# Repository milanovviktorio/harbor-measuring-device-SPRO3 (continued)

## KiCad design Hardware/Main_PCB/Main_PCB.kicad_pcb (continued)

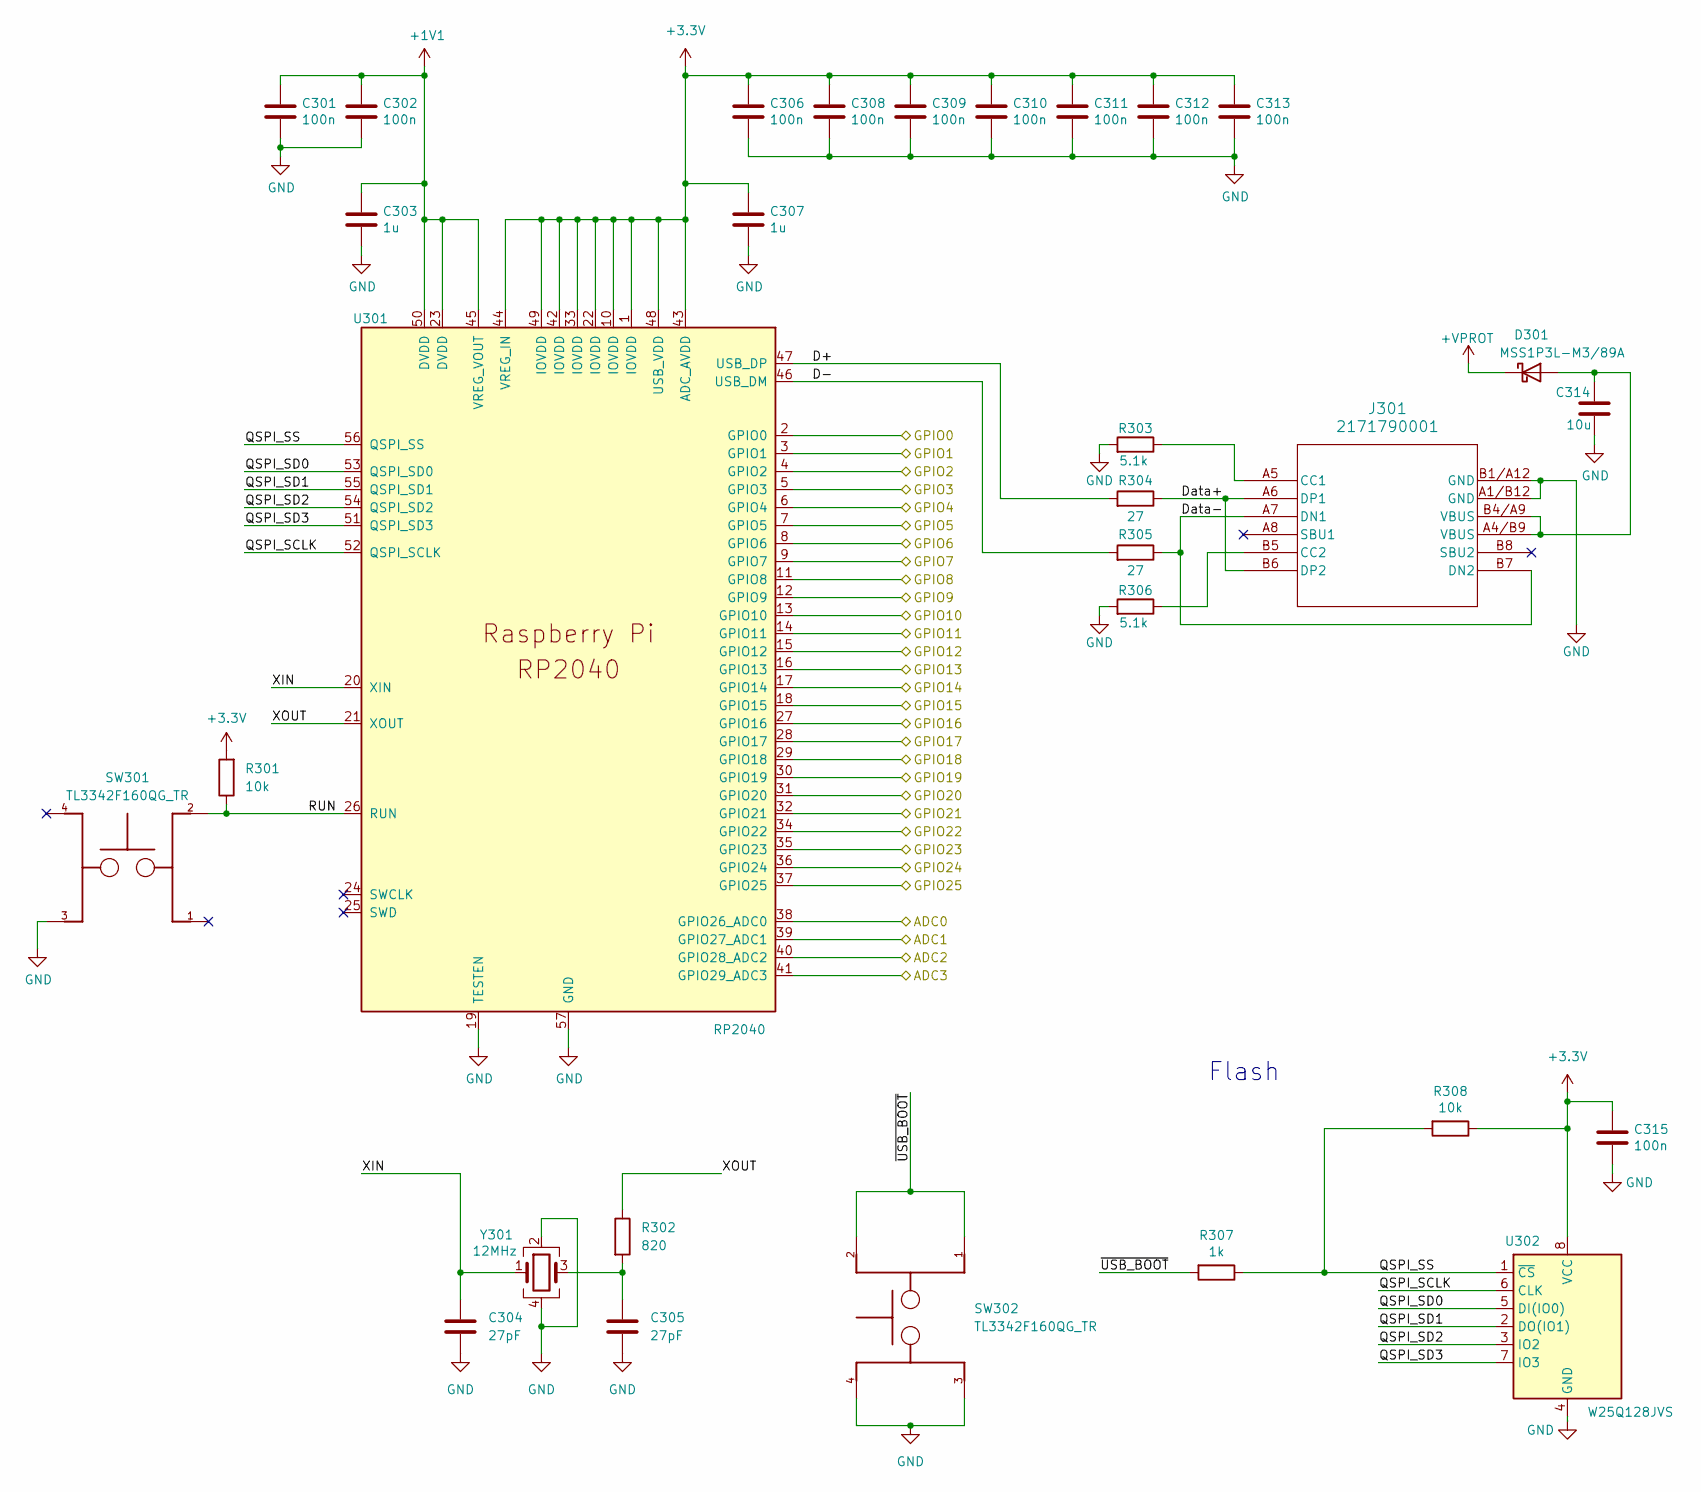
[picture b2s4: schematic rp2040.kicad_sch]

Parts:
C301, C302, C306, C308, C309, C310, C311, C312, C313, C315: 100n; C_0603_1608Metric_Pad1.08x0.95mm_HandSolder
C303, C307: 1u; C_0603_1608Metric_Pad1.08x0.95mm_HandSolder
C304, C305: 27pF; C_0603_1608Metric_Pad1.08x0.95mm_HandSolder
C314: 10u; C_0603_1608Metric_Pad1.08x0.95mm_HandSolder
D301: MSS1P3L-M3/89A; Vishay_SMPA
J301: 2171790001; 2171790001_MOL
R301: 10k; C_0603_1608Metric_Pad1.08x0.95mm_HandSolder
R302: 820; R_0603_1608Metric_Pad0.98x0.95mm_HandSolder
R303, R306: 5.1k; R_0603_1608Metric_Pad0.98x0.95mm_HandSolder
R304, R305: 27; R_0603_1608Metric_Pad0.98x0.95mm_HandSolder
R307: 1k; R_0603_1608Metric_Pad0.98x0.95mm_HandSolder
R308: 10k; R_0603_1608Metric_Pad0.98x0.95mm_HandSolder
SW301, SW302: TL3342F160QG_TR; SW_TL3342F160QG_TR
U301: RP2040; QFN-56-1EP_7x7mm_P0.4mm_EP3.2x3.2mm
U302: W25Q128JVS; SOIC-8_5.3x5.3mm_P1.27mm
Y301: 12MHz; Crystal_SMD_Abracon_ABM8G-4Pin_3.2x2.5mm

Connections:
+1V1: C301.1, C302.1, C303.1, U301.23 (DVDD), U301.45 (VREG_VOUT), U301.50 (DVDD)
+3.3V: C306.1, C307.1, C308.1, C309.1, C310.1, C311.1, C312.1, C313.1, C315.1, R301.2, R308.1, U301.1 (IOVDD), U301.10 (IOVDD), U301.22 (IOVDD), U301.33 (IOVDD), U301.42 (IOVDD), U301.43 (ADC_AVDD), U301.44 (VREG_IN), U301.48 (USB_VDD), U301.49 (IOVDD), U302.8 (VCC); also elsewhere on the board
+VPROT: D301.1 (K); also elsewhere on the board
/AHS: U301.37 (GPIO25); also elsewhere on the board
/ALS: U301.36 (GPIO24); also elsewhere on the board
/BEMF: U301.8 (GPIO6); also elsewhere on the board
/BHS: U301.35 (GPIO23); also elsewhere on the board
/BLS: U301.34 (GPIO22); also elsewhere on the board
/CE: U301.9 (GPIO7); also elsewhere on the board
/CHS: U301.32 (GPIO21); also elsewhere on the board
/CLS: U301.31 (GPIO20); also elsewhere on the board
/CSN: U301.11 (GPIO8); also elsewhere on the board
/ICM42688 - Gyro/AP_CS: U301.12 (GPIO9); also elsewhere on the board
/ICM42688 - Gyro/AP_SCL: U301.14 (GPIO11); also elsewhere on the board
/ICM42688 - Gyro/AP_SDA: U301.13 (GPIO10); also elsewhere on the board
/ICM42688 - Gyro/AP_SDO: U301.16 (GPIO13); also elsewhere on the board
/ICM42688 - Gyro/INT1: U301.15 (GPIO12); also elsewhere on the board
/MISO: U301.27 (GPIO16); also elsewhere on the board
/MOSI: U301.30 (GPIO19); also elsewhere on the board
/OUT3: U301.17 (GPIO14); also elsewhere on the board
/OUT4: U301.18 (GPIO15); also elsewhere on the board
/Power supply unit/Battery_voltage_level: U301.39 (GPIO27_ADC1); also elsewhere on the board
/RP2040/ADC0: U301.38 (GPIO26_ADC0); also elsewhere on the board
/RP2040/ADC2: U301.40 (GPIO28_ADC2)
/RP2040/ADC3: U301.41 (GPIO29_ADC3)
/RP2040/D+: R304.2, U301.47 (USB_DP)
/RP2040/D-: R305.2, U301.46 (USB_DM)
/RP2040/Data+: J301.A6 (DP1), J301.B6 (DP2), R304.1
/RP2040/Data-: J301.A7 (DN1), J301.B7 (DN2), R305.1
/RP2040/GPIO0: U301.2 (GPIO0); also elsewhere on the board
/RP2040/GPIO1: U301.3 (GPIO1); also elsewhere on the board
/RP2040/GPIO2: U301.4 (GPIO2); also elsewhere on the board
/RP2040/GPIO3: U301.5 (GPIO3); also elsewhere on the board
/RP2040/GPIO4: U301.6 (GPIO4); also elsewhere on the board
/RP2040/GPIO5: U301.7 (GPIO5); also elsewhere on the board
/RP2040/QSPI_SCLK: U301.52 (QSPI_SCLK), U302.6 (CLK)
/RP2040/QSPI_SD0: U301.53 (QSPI_SD0), U302.5 (DI(IO0))
/RP2040/QSPI_SD1: U301.55 (QSPI_SD1), U302.2 (DO(IO1))
/RP2040/QSPI_SD2: U301.54 (QSPI_SD2), U302.3 (IO2)
/RP2040/QSPI_SD3: U301.51 (QSPI_SD3), U302.7 (IO3)
/RP2040/QSPI_SS: R307.1, R308.2, U301.56 (QSPI_SS), U302.1 (~CS)
/RP2040/RUN: R301.1, SW301.2, U301.26 (RUN)
/RP2040/XIN: C304.1, U301.20 (XIN), Y301.1
/RP2040/XOUT: R302.1, U301.21 (XOUT)
/RP2040/~USB_BOOT: R307.2, SW302.1, SW302.2
/SCK: U301.29 (GPIO18); also elsewhere on the board
/Servo_In: U301.28 (GPIO17); also elsewhere on the board
GND: C301.2, C302.2, C303.2, C304.2, C305.2, C306.2, C307.2, C308.2, C309.2, C310.2, C311.2, C312.2, C313.2, C314.2, C315.2, J301.A1/B12 (GND), J301.B1/A12 (GND), R303.2, R306.2, SW301.3, SW302.3, SW302.4, U301.19 (TESTEN), U301.57 (GND), U302.4 (GND), Y301.2, Y301.4; also elsewhere on the board
unnamed: C305.1, R302.2, Y301.3
unnamed: C314.1, D301.2 (A), J301.A4/B9 (VBUS), J301.B4/A9 (VBUS)
unnamed: J301.A5 (CC1), R303.1
unnamed: J301.B5 (CC2), R306.1

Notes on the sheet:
Flash

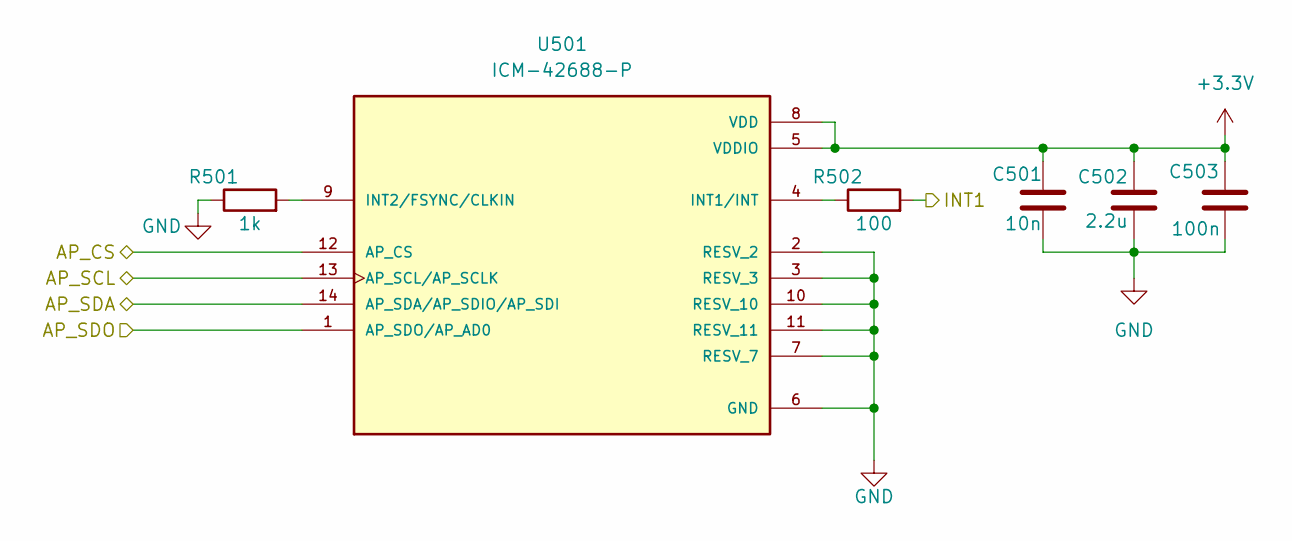
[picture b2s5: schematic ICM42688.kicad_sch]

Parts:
C501: 10n; C_0805_2012Metric_Pad1.18x1.45mm_HandSolder
C502: 2.2u; C_0805_2012Metric_Pad1.18x1.45mm_HandSolder
C503: 100n; C_0805_2012Metric_Pad1.18x1.45mm_HandSolder
R501: 1k; R_0603_1608Metric_Pad0.98x0.95mm_HandSolder
R502: 100; R_0603_1608Metric_Pad0.98x0.95mm_HandSolder
U501: ICM-42688-P; PQFN50P300X250X97-14N; PARTREV 1.2

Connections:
+3.3V: C501.1, C502.2, C503.2, U501.5 (VDDIO), U501.8 (VDD); also elsewhere on the board
/ICM42688 - Gyro/AP_CS: U501.12 (AP_CS); also elsewhere on the board
/ICM42688 - Gyro/AP_SCL: U501.13 (AP_SCL/AP_SCLK); also elsewhere on the board
/ICM42688 - Gyro/AP_SDA: U501.14 (AP_SDA/AP_SDIO/AP_SDI); also elsewhere on the board
/ICM42688 - Gyro/AP_SDO: U501.1 (AP_SDO/AP_AD0); also elsewhere on the board
/ICM42688 - Gyro/INT1: R502.2; also elsewhere on the board
GND: C501.2, C502.1, C503.1, R501.1, U501.2 (RESV_2), U501.3 (RESV_3), U501.6 (GND), U501.7 (RESV_7), U501.10 (RESV_10), U501.11 (RESV_11); also elsewhere on the board
unnamed: R502.1, U501.4 (INT1/INT)
unnamed: R501.2, U501.9 (INT2/FSYNC/CLKIN)

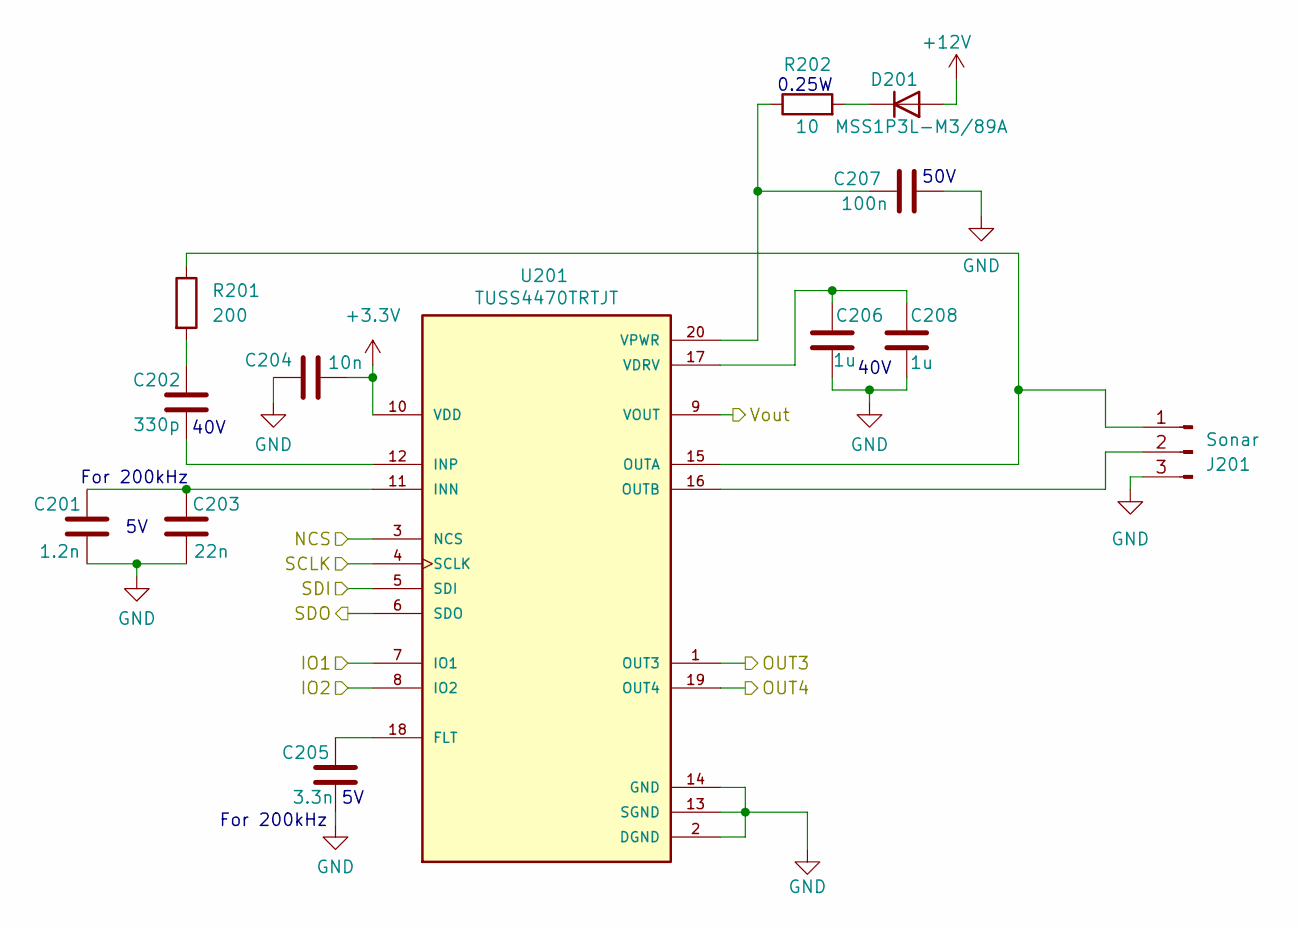
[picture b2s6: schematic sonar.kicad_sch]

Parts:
C201: 1.2n; C_0603_1608Metric_Pad1.08x0.95mm_HandSolder
C202: 330p; C_0805_2012Metric_Pad1.18x1.45mm_HandSolder
C203: 22n; C_0603_1608Metric_Pad1.08x0.95mm_HandSolder
C204: 10n; C_0805_2012Metric_Pad1.18x1.45mm_HandSolder
C205: 3.3n; C_0805_2012Metric_Pad1.18x1.45mm_HandSolder
C206, C208: 1u; C_0603_1608Metric_Pad1.08x0.95mm_HandSolder
C207: 100n; C_0805_2012Metric_Pad1.18x1.45mm_HandSolder
D201: MSS1P3L-M3/89A; Vishay_SMPA
J201: Sonar; JST_PH_B3B-PH-K_1x03_P2.00mm_Vertical
R201: 200; R_0603_1608Metric_Pad0.98x0.95mm_HandSolder
R202: 10; C_0805_2012Metric_Pad1.18x1.45mm_HandSolder
U201: TUSS4470TRTJT; QFN50P400X400X80-21N; PARTREV December 2019

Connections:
+3.3V: C204.1, U201.10 (VDD); also elsewhere on the board
+12V: D201.2 (A); also elsewhere on the board
/OUT3: U201.1 (OUT3); also elsewhere on the board
/OUT4: U201.19 (OUT4); also elsewhere on the board
/RP2040/ADC0: U201.9 (VOUT); also elsewhere on the board
/RP2040/GPIO0: U201.4 (SCLK); also elsewhere on the board
/RP2040/GPIO1: U201.3 (NCS); also elsewhere on the board
/RP2040/GPIO2: U201.6 (SDO); also elsewhere on the board
/RP2040/GPIO3: U201.5 (SDI); also elsewhere on the board
/RP2040/GPIO4: U201.7 (IO1); also elsewhere on the board
/RP2040/GPIO5: U201.8 (IO2); also elsewhere on the board
GND: C201.1, C203.1, C204.2, C205.1, C206.1, C207.2, C208.1, J201.3, U201.2 (DGND), U201.13 (SGND), U201.14 (GND); also elsewhere on the board
unnamed: C202.2, R201.2
unnamed: D201.1 (K), R202.2
unnamed: J201.1, R201.1, U201.15 (OUTA)
unnamed: J201.2, U201.16 (OUTB)
unnamed: C205.2, U201.18 (FLT)
unnamed: C201.2, C203.2, U201.11 (INN)
unnamed: C202.1, U201.12 (INP)
unnamed: C206.2, C208.2, U201.17 (VDRV)
unnamed: C207.1, R202.1, U201.20 (VPWR)

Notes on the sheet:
40V
50V
For 200kHz
0.25W

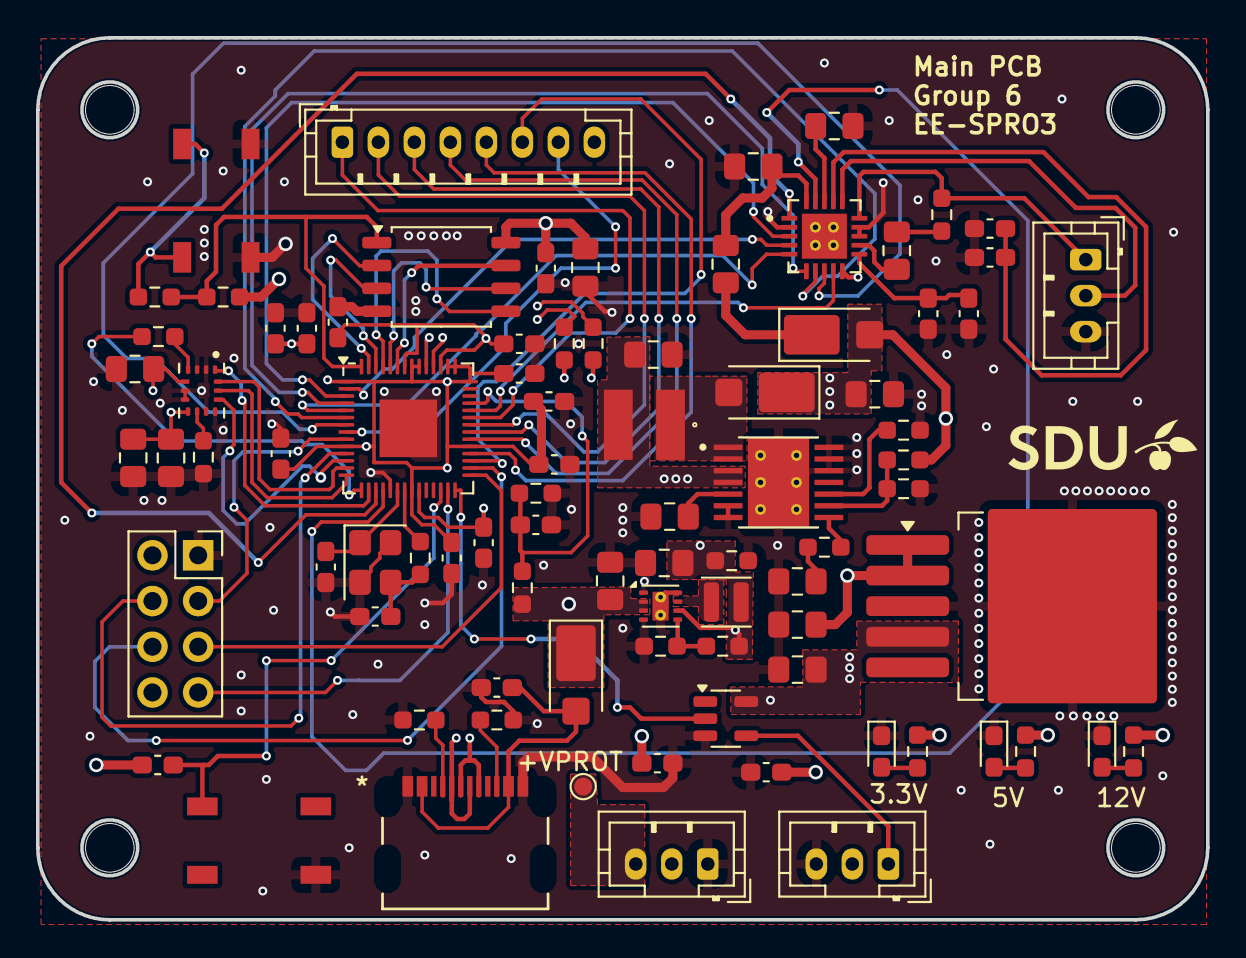
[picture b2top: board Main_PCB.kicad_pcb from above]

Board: 4 copper layers, 65.0 x 49.0 mm, 90 parts (0 on the bottom side), 75 nets.

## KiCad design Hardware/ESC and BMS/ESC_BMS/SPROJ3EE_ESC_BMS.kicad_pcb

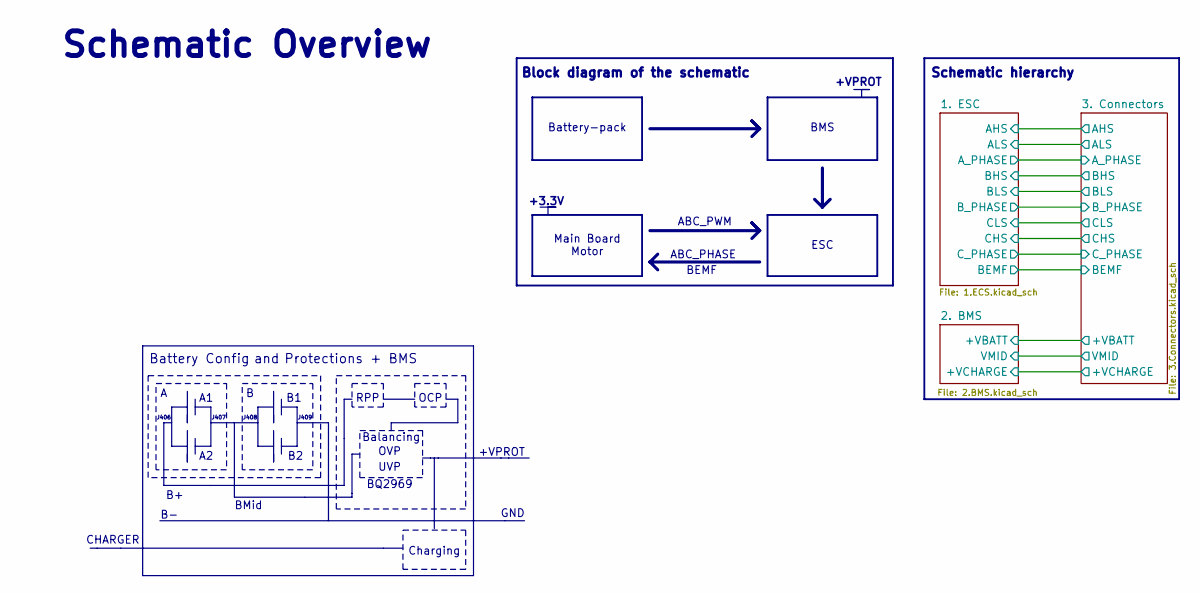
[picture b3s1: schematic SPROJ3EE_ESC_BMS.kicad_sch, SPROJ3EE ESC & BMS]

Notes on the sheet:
UVP
Schematic Overview
J409
J406
Balancing
J407
Protections + BMS
Battery Config
OCP
CHARGER
+VPROT
+3.3V
Charging
Schematic hierarchy
Battery-pack
and
Main Board Motor
J408
ABC_PWM
RPP
Block diagram of the schematic
GND
ABC_PHASE
BQ2969
BEMF
ESC
OVP
BMid
BMS

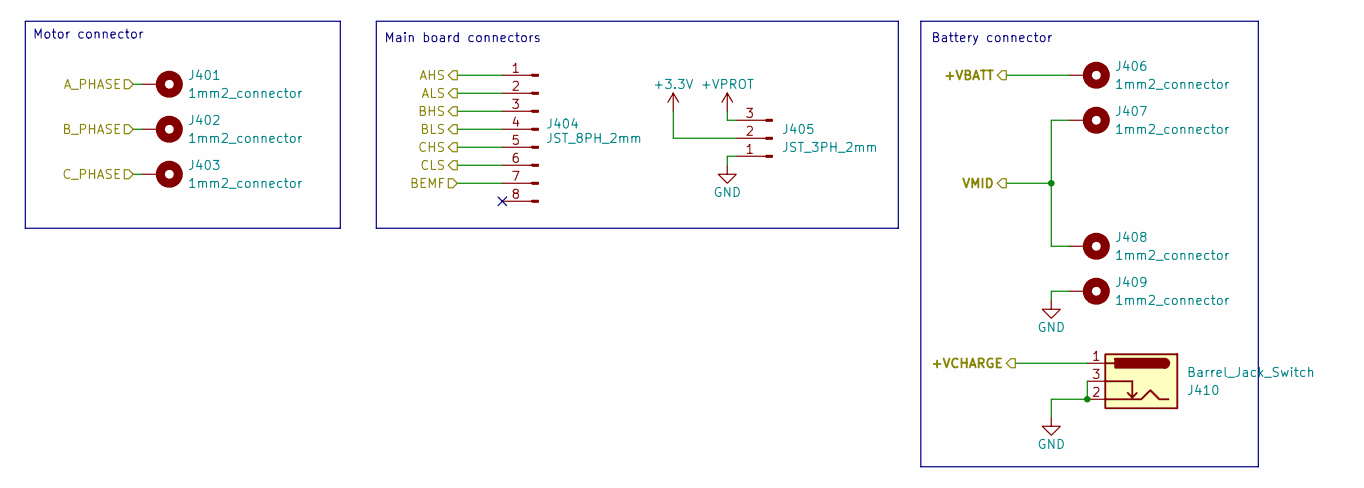
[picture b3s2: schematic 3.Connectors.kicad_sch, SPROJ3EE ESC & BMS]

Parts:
J401, J402, J403, J406, J407, J408, J409: 1mm2_connector; SolderWire-1sqmm_1x01_D1.4mm_OD2.7mm
J404: JST_8PH_2mm; JST_PH_B8B-PH-K_1x08_P2.00mm_Vertical
J405: JST_3PH_2mm; JST_PH_B3B-PH-K_1x03_P2.00mm_Vertical
J410: Barrel_Jack_Switch; BarrelJack_Horizontal

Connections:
+3.3V: J405.2; also elsewhere on the board
+VPROT: J405.3; also elsewhere on the board
/1. ESC/AHS: J404.1; also elsewhere on the board
/1. ESC/ALS: J404.2; also elsewhere on the board
/1. ESC/BEMF: J404.7; also elsewhere on the board
/1. ESC/BHS: J404.3; also elsewhere on the board
/1. ESC/BLS: J404.4; also elsewhere on the board
/1. ESC/CHS: J404.5; also elsewhere on the board
/1. ESC/CLS: J404.6; also elsewhere on the board
/2. BMS/+VBATT: J406.1; also elsewhere on the board
/2. BMS/+VCHARGE: J410.1; also elsewhere on the board
/2. BMS/VMID: J407.1, J408.1; also elsewhere on the board
A_PHASE: J401.1; also elsewhere on the board
B_PHASE: J402.1; also elsewhere on the board
C_PHASE: J403.1; also elsewhere on the board
GND: J405.1, J409.1, J410.2, J410.3; also elsewhere on the board

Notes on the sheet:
Main board connectors
Motor connector
Battery connector

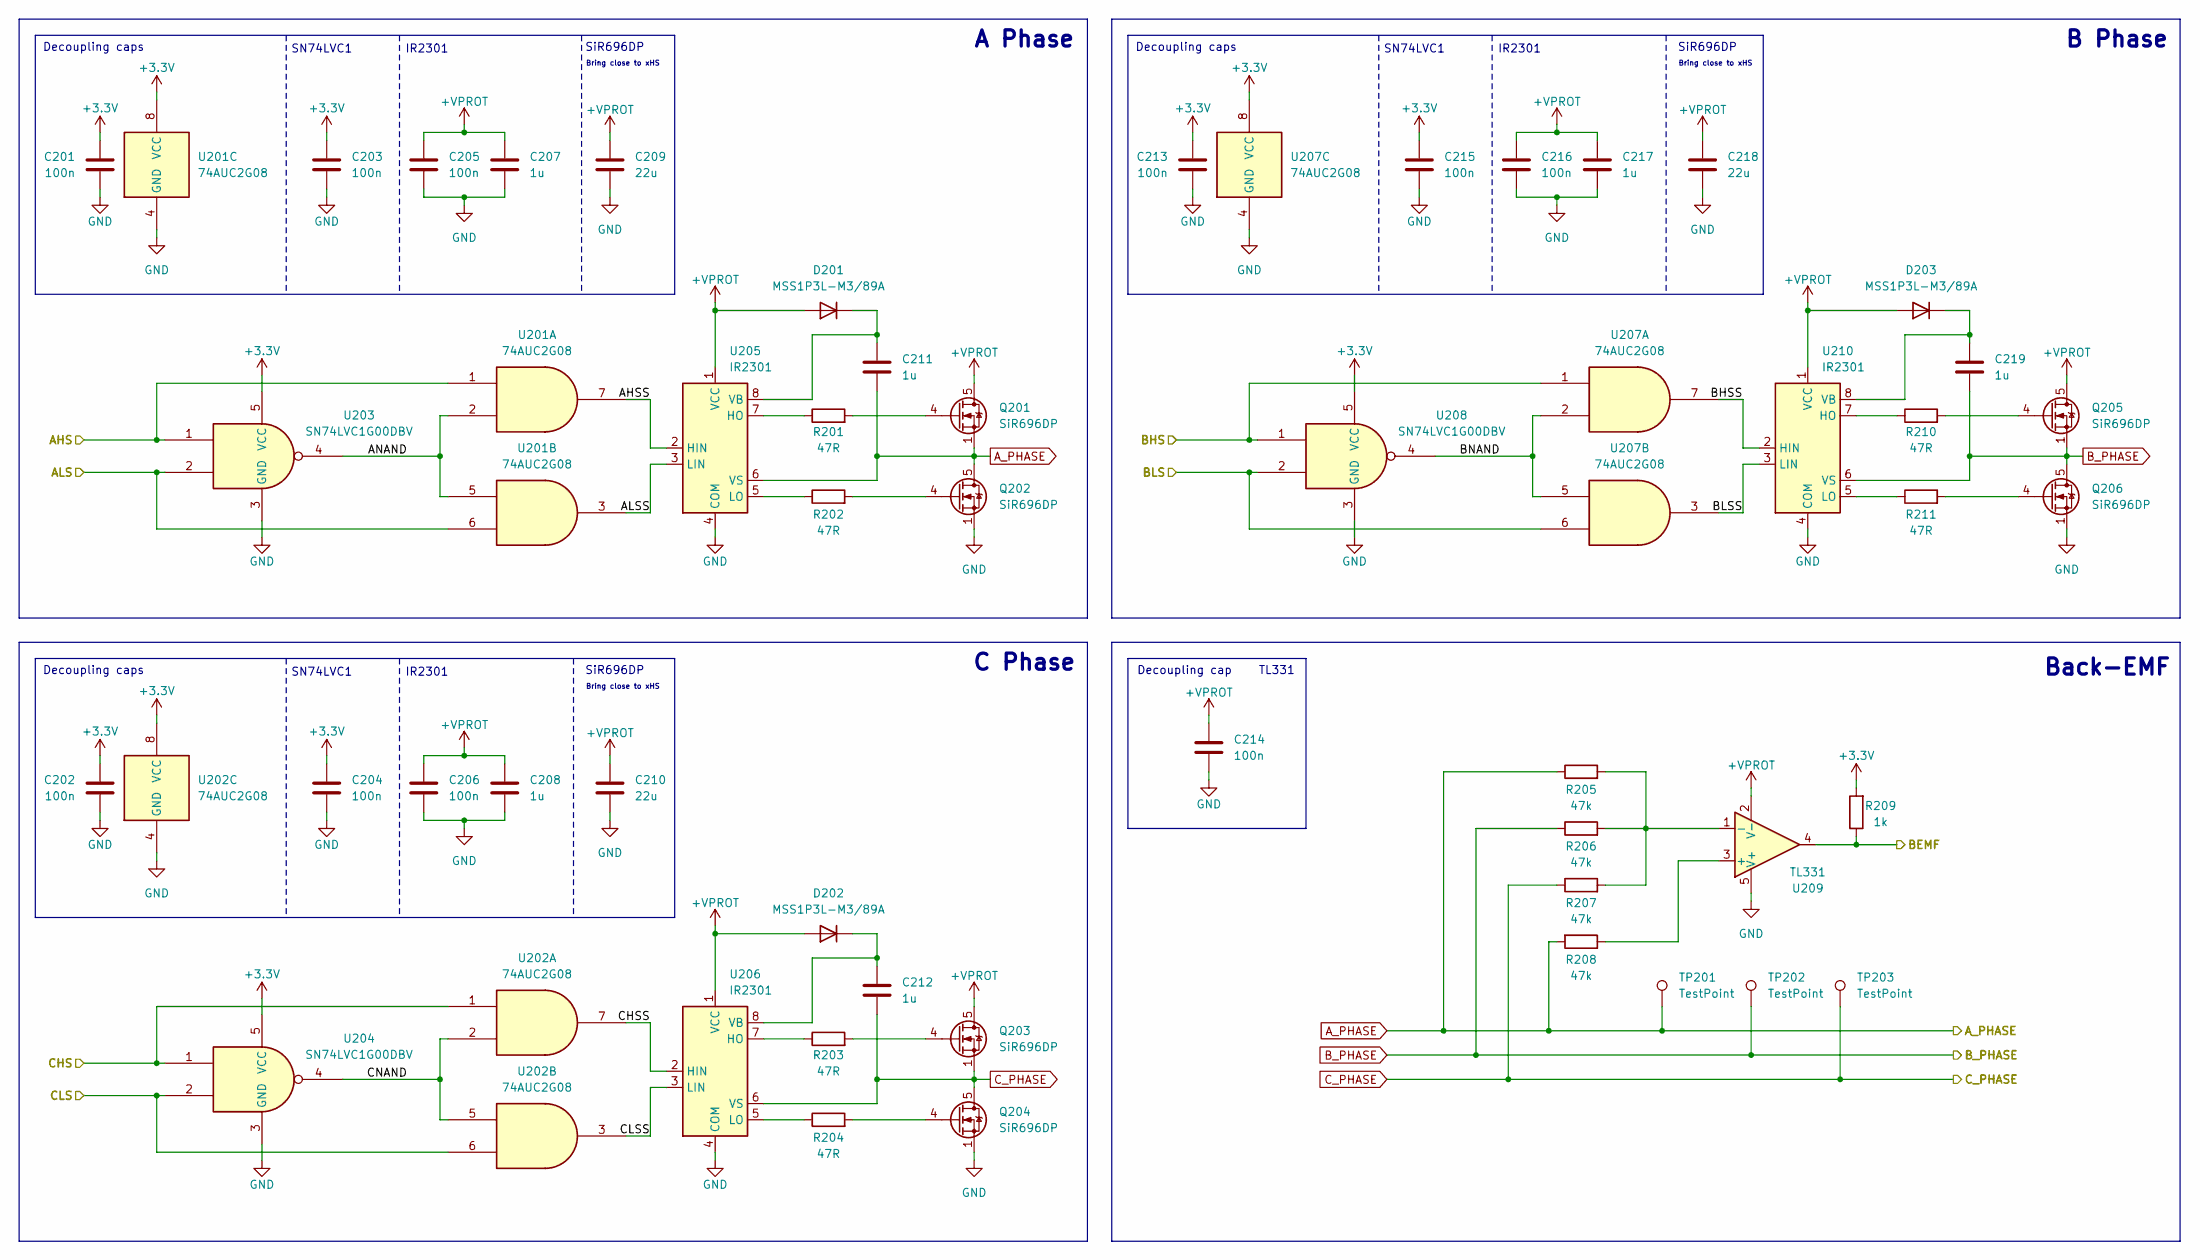
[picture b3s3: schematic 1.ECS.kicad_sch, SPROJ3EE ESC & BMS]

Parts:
C201, C202, C203, C204, C205, C206, C213, C214, C215, C216: 100n; C_0603_1608Metric
C207, C208, C211, C212, C217, C219: 1u; C_0603_1608Metric
C209, C210, C218: 22u; C_0805_2012Metric_Pad1.18x1.45mm_HandSolder
D201, D202, D203: MSS1P3L-M3/89A; Vishay_SMPA
Q201, Q202, Q203, Q204, Q205, Q206: SiR696DP; PowerPAK_SO-8_Single
R201, R202, R203, R204, R210, R211: 47R; R_0603_1608Metric
R205, R206, R207, R208: 47k; R_0603_1608Metric
R209: 1k; R_0603_1608Metric
TP201, TP202, TP203: TestPoint; TestPoint_Pad_D1.0mm
U201, U202, U207: 74AUC2G08; SSOP-8_2.95x2.8mm_P0.65mm
U203, U204, U208: SN74LVC1G00DBV; SOT-23-5
U205, U206, U210: IR2301; SOIC-8_3.9x4.9mm_P1.27mm
U209: TL331; SOT-23-5

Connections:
+3.3V: C201.1, C202.1, C203.1, C204.1, C213.1, C215.1, R209.2, U201.8 (VCC), U202.8 (VCC), U203.5 (VCC), U204.5 (VCC), U207.8 (VCC), U208.5 (VCC); also elsewhere on the board
+VPROT: C205.1, C206.1, C207.1, C208.1, C209.1, C210.1, C214.1, C216.1, C217.1, C218.1, D201.2 (A), D202.2 (A), D203.2 (A), Q201.5 (D), Q203.5 (D), Q205.5 (D), U205.1 (VCC), U206.1 (VCC), U209.2 (V-), U210.1 (VCC); also elsewhere on the board
/1. ESC/AHS: U201.1, U203.1; also elsewhere on the board
/1. ESC/AHSS: U201.7, U205.2 (HIN)
/1. ESC/ALS: U201.6, U203.2; also elsewhere on the board
/1. ESC/ALSS: U201.3, U205.3 (LIN)
/1. ESC/ANAND: U201.2, U201.5, U203.4
/1. ESC/BEMF: R209.1, U209.4; also elsewhere on the board
/1. ESC/BHS: U207.1, U208.1; also elsewhere on the board
/1. ESC/BHSS: U207.7, U210.2 (HIN)
/1. ESC/BLS: U207.6, U208.2; also elsewhere on the board
/1. ESC/BLSS: U207.3, U210.3 (LIN)
/1. ESC/BNAND: U207.2, U207.5, U208.4
/1. ESC/CHS: U202.1, U204.1; also elsewhere on the board
/1. ESC/CHSS: U202.7, U206.2 (HIN)
/1. ESC/CLS: U202.6, U204.2; also elsewhere on the board
/1. ESC/CLSS: U202.3, U206.3 (LIN)
/1. ESC/CNAND: U202.2, U202.5, U204.4
A_PHASE: C211.2, Q201.1 (S), Q201.2 (S), Q201.3 (S), Q202.5 (D), R205.1, R208.2, TP201.1, U205.6 (VS); also elsewhere on the board
B_PHASE: C219.2, Q205.1 (S), Q205.2 (S), Q205.3 (S), Q206.5 (D), R206.1, TP202.1, U210.6 (VS); also elsewhere on the board
C_PHASE: C212.2, Q203.1 (S), Q203.2 (S), Q203.3 (S), Q204.5 (D), R207.1, TP203.1, U206.6 (VS); also elsewhere on the board
GND: C201.2, C202.2, C203.2, C204.2, C205.2, C206.2, C207.2, C208.2, C209.2, C210.2, C213.2, C214.2, C215.2, C216.2, C217.2, C218.2, Q202.1 (S), Q202.2 (S), Q202.3 (S), Q204.1 (S), Q204.2 (S), Q204.3 (S), Q206.1 (S), Q206.2 (S), Q206.3 (S), U201.4 (GND), U202.4 (GND), U203.3 (GND), U204.3 (GND), U205.4 (COM), U206.4 (COM), U207.4 (GND), U208.3 (GND), U209.5 (V+), U210.4 (COM); also elsewhere on the board
unnamed: C211.1, D201.1 (K), U205.8 (VB)
unnamed: C212.1, D202.1 (K), U206.8 (VB)
unnamed: C219.1, D203.1 (K), U210.8 (VB)
unnamed: Q201.4 (G), R201.2
unnamed: Q202.4 (G), R202.2
unnamed: Q203.4 (G), R203.2
unnamed: Q204.4 (G), R204.2
unnamed: Q205.4 (G), R210.2
unnamed: Q206.4 (G), R211.2
unnamed: R201.1, U205.7 (HO)
unnamed: R202.1, U205.5 (LO)
unnamed: R203.1, U206.7 (HO)
unnamed: R204.1, U206.5 (LO)
unnamed: R208.1, U209.3 (+)
unnamed: R205.2, R206.2, R207.2, U209.1 (-)
unnamed: R210.1, U210.7 (HO)
unnamed: R211.1, U210.5 (LO)

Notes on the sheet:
Bring close to xHS
C Phase
SiR696DP
SN74LVC1
Decoupling caps
TL331
IR2301
B Phase
Back-EMF
A Phase
Decoupling cap

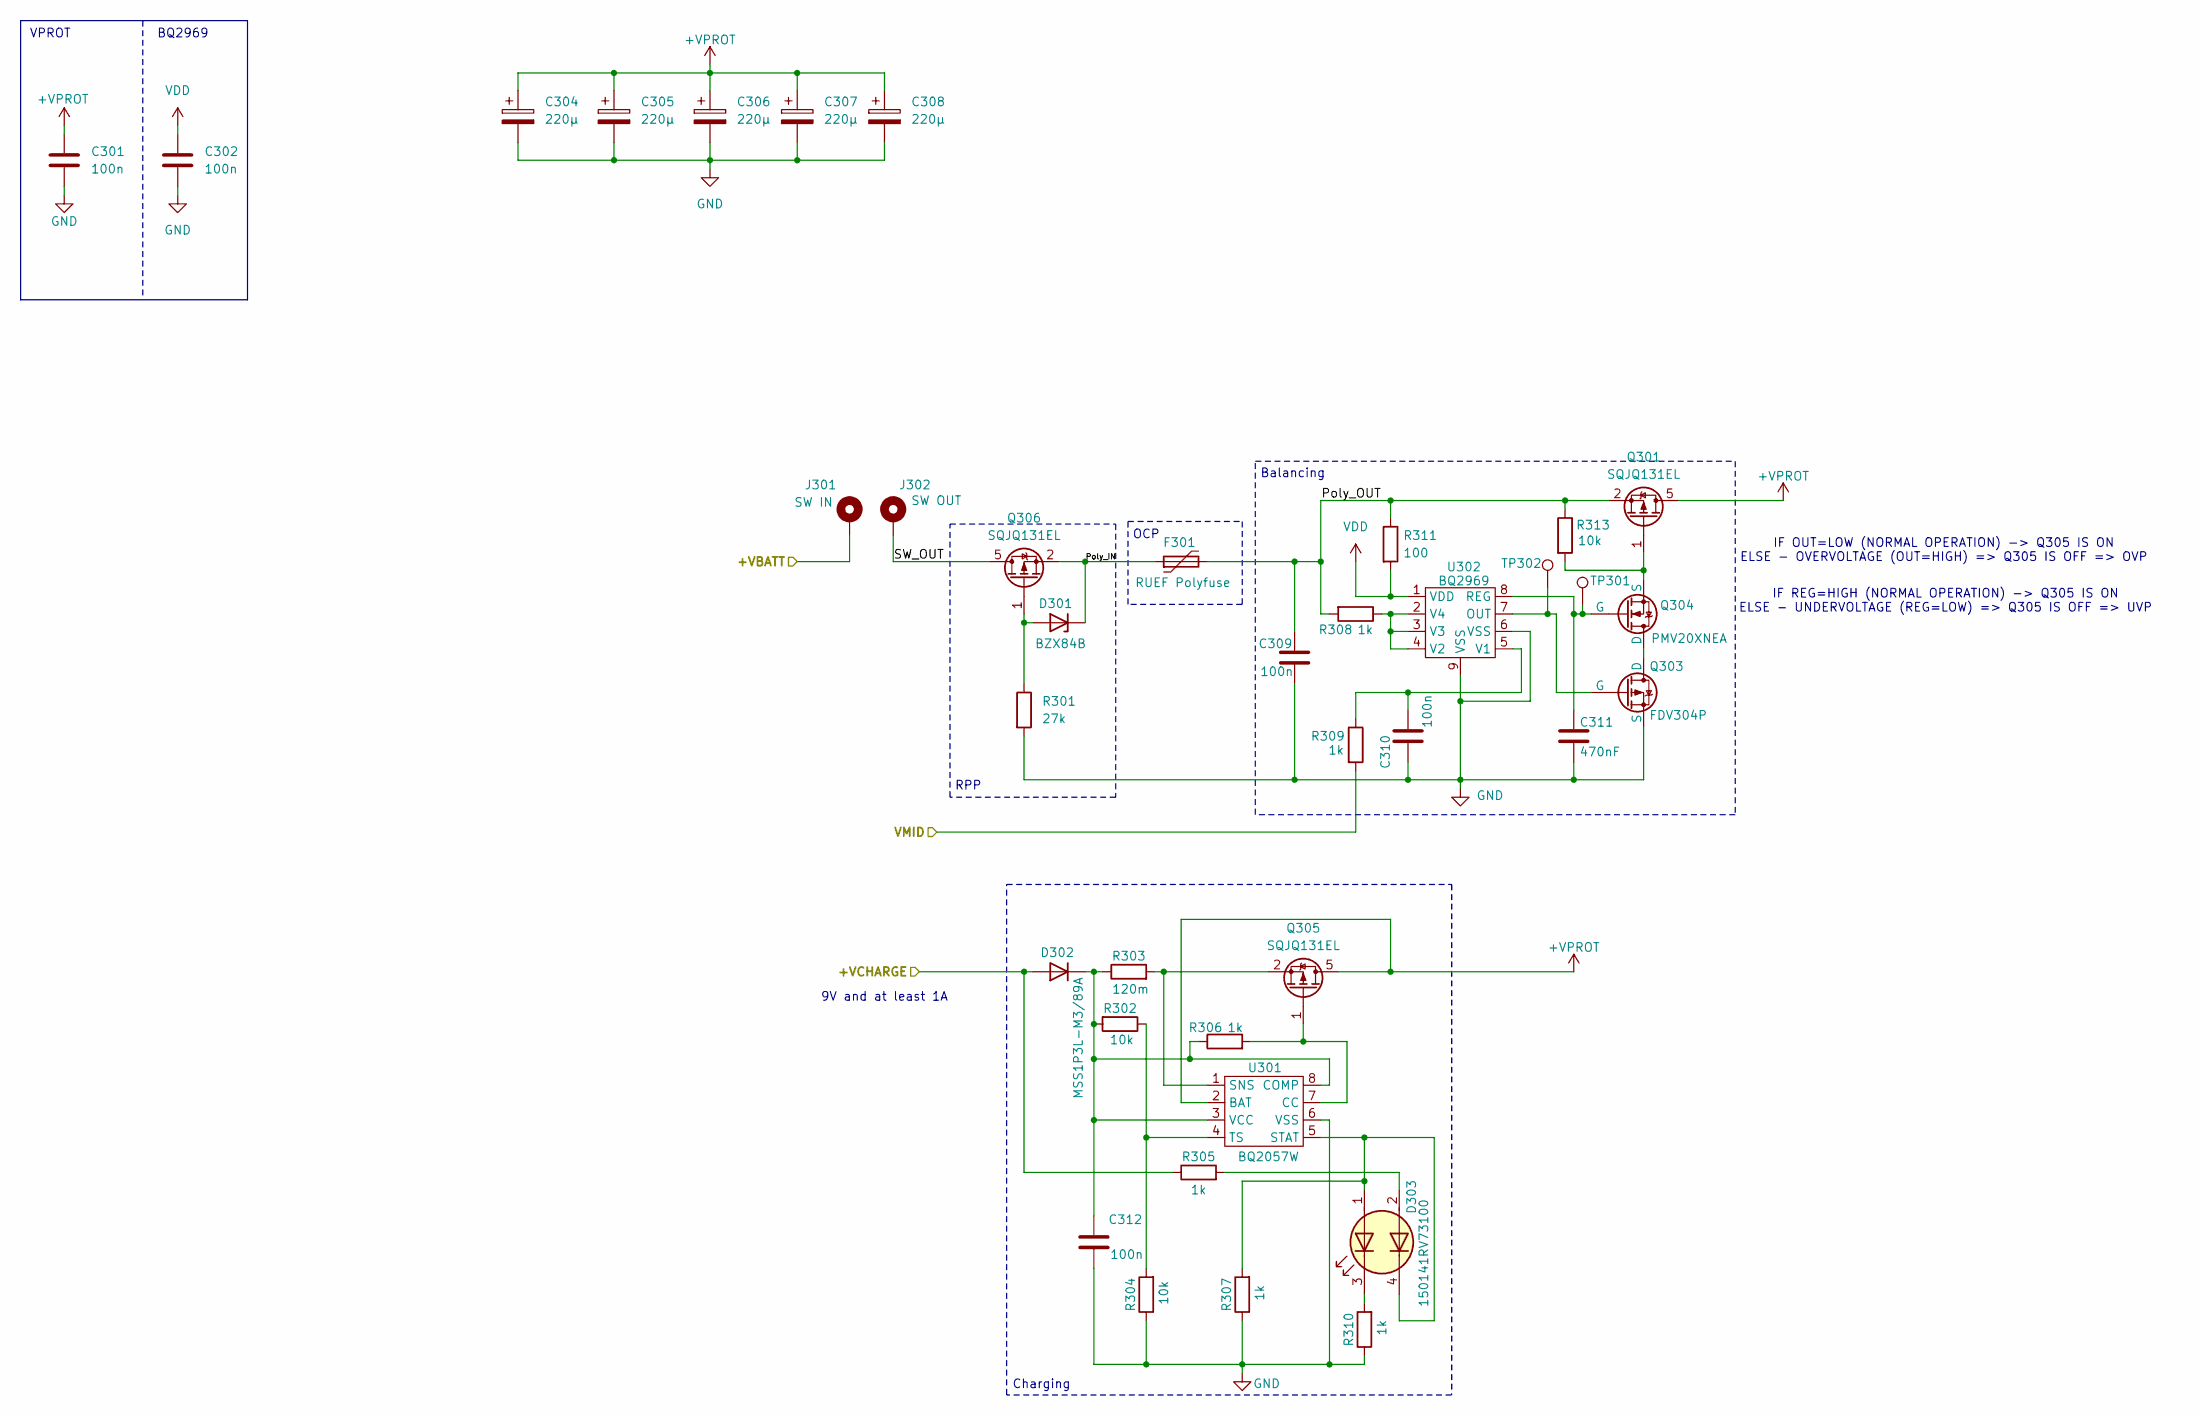
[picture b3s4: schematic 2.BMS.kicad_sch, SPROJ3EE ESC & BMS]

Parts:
C301, C309, C310: 100n; C_0603_1608Metric
C302: 100n; C_0603_1608Metric_Pad1.08x0.95mm_HandSolder
C304, C305, C306, C307, C308: 220µ; CP_Elec_6.3x5.9
C311: 470nF; C_0603_1608Metric_Pad1.08x0.95mm_HandSolder
C312: 100n; C_0805_2012Metric_Pad1.18x1.45mm_HandSolder
D301: BZX84B; SOT-23
D302: MSS1P3L-M3/89A; Vishay_SMPA
D303: 150141RV73100; LED_RGB_Wuerth-PLCC4_3.2x2.8mm_150141M173100
F301: RUEF Polyfuse; R_Axial_DIN0207_L6.3mm_D2.5mm_P10.16mm_Horizontal
J301: SW IN; SolderWire-1sqmm_1x01_D1.4mm_OD2.7mm
J302: SW OUT; SolderWire-1sqmm_1x01_D1.4mm_OD2.7mm
Q301, Q305, Q306: SQJQ131EL; PowerPAK_SO-8L_Single
Q303: FDV304P; SOT-23
Q304: PMV20XNEA; SOT-23
R301: 27k; R_0603_1608Metric
R302, R304, R313: 10k; R_0603_1608Metric
R303: 120m; R_0805_2012Metric_Pad1.20x1.40mm_HandSolder
R305, R306, R307, R308, R309, R310: 1k; R_0603_1608Metric
R311: 100; R_0603_1608Metric
TP301, TP302: TestPoint; TestPoint_Pad_D1.0mm
U301: BQ2057W; SOIC-8_5.3x5.3mm_P1.27mm
U302: BQ2969; WSON-8-1EP_3x3mm_P0.5mm_EP1.2x2mm_ThermalVias

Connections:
+VPROT: C301.1, C304.1, C305.1, C306.1, C307.1, C308.1, Q301.5 (D), Q305.5 (D), U301.2 (BAT); also elsewhere on the board
/2. BMS/+VBATT: J301.1; also elsewhere on the board
/2. BMS/+VCHARGE: D302.2 (A), R305.1; also elsewhere on the board
/2. BMS/Poly_IN: D301.1 (K), F301.1, Q306.2 (S), Q306.3 (S), Q306.4 (S)
/2. BMS/Poly_OUT: C309.1, F301.2, Q301.2 (S), Q301.3 (S), Q301.4 (S), R308.2, R311.1, R313.1
/2. BMS/SW_OUT: J302.1, Q306.5 (D)
/2. BMS/VMID: R309.2; also elsewhere on the board
GND: C301.2, C302.2, C304.2, C305.2, C306.2, C307.2, C308.2, C309.2, C310.1, C311.2, C312.2, Q303.3 (S), R301.2, R304.1, R307.1, R310.1, U301.6 (VSS), U302.6 (VSS), U302.9 (VSS); also elsewhere on the board
unnamed: D301.2 (A), Q306.1 (G), R301.1
unnamed: C312.1, D302.1 (K), R302.2, R303.1, R306.1, U301.3 (VCC), U301.8 (COMP)
unnamed: D303.1 (A1), D303.4 (K2), R307.2, U301.5 (STAT)
unnamed: D303.2 (A2), R305.2
unnamed: D303.3 (K1), R310.2
unnamed: Q301.1 (G), Q304.3 (S), R313.2
unnamed: Q303.1 (D), Q304.1 (D)
unnamed: Q303.2 (G), TP302.1, U302.7 (OUT)
unnamed: C311.1, Q304.2 (G), TP301.1, U302.8 (REG)
unnamed: Q305.1 (G), R306.2, U301.7 (CC)
unnamed: Q305.2 (S), Q305.3 (S), Q305.4 (S), R303.2, U301.1 (SNS)
unnamed: R302.1, R304.2, U301.4 (TS)
unnamed: C310.2, R309.1, U302.5 (V1)
unnamed: R308.1, U302.2 (V4), U302.3 (V3), U302.4 (V2)
VDD: C302.1, R311.2, U302.1 (VDD)

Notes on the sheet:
9V and at least 1A
IF OUT=LOW (NORMAL OPERATION) -> Q305 IS ON ELSE - OVERVOLTAGE (OUT=HIGH) => Q305 IS OFF => OVP
IF REG=HIGH (NORMAL OPERATION) -> Q305 IS ON ELSE - UNDERVOLTAGE (REG=LOW) => Q305 IS OFF => UVP
Charging
VPROT
OCP
BQ2969
Balancing
RPP

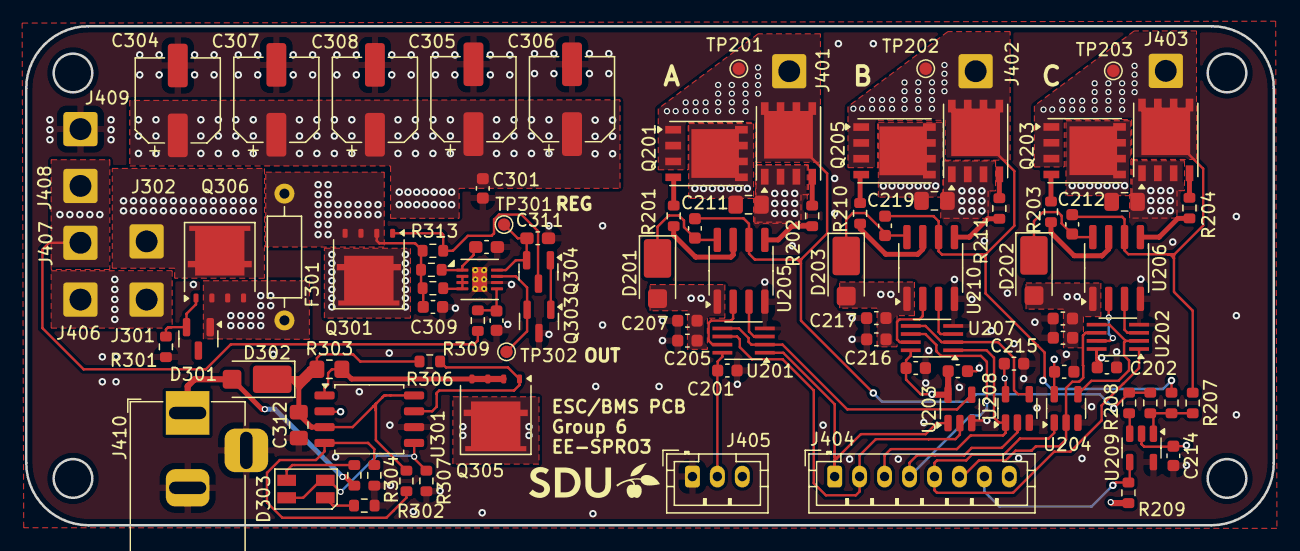
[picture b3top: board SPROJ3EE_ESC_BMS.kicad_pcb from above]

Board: 4 copper layers, 100.0 x 40.0 mm, 100 parts (0 on the bottom side), 60 nets.
